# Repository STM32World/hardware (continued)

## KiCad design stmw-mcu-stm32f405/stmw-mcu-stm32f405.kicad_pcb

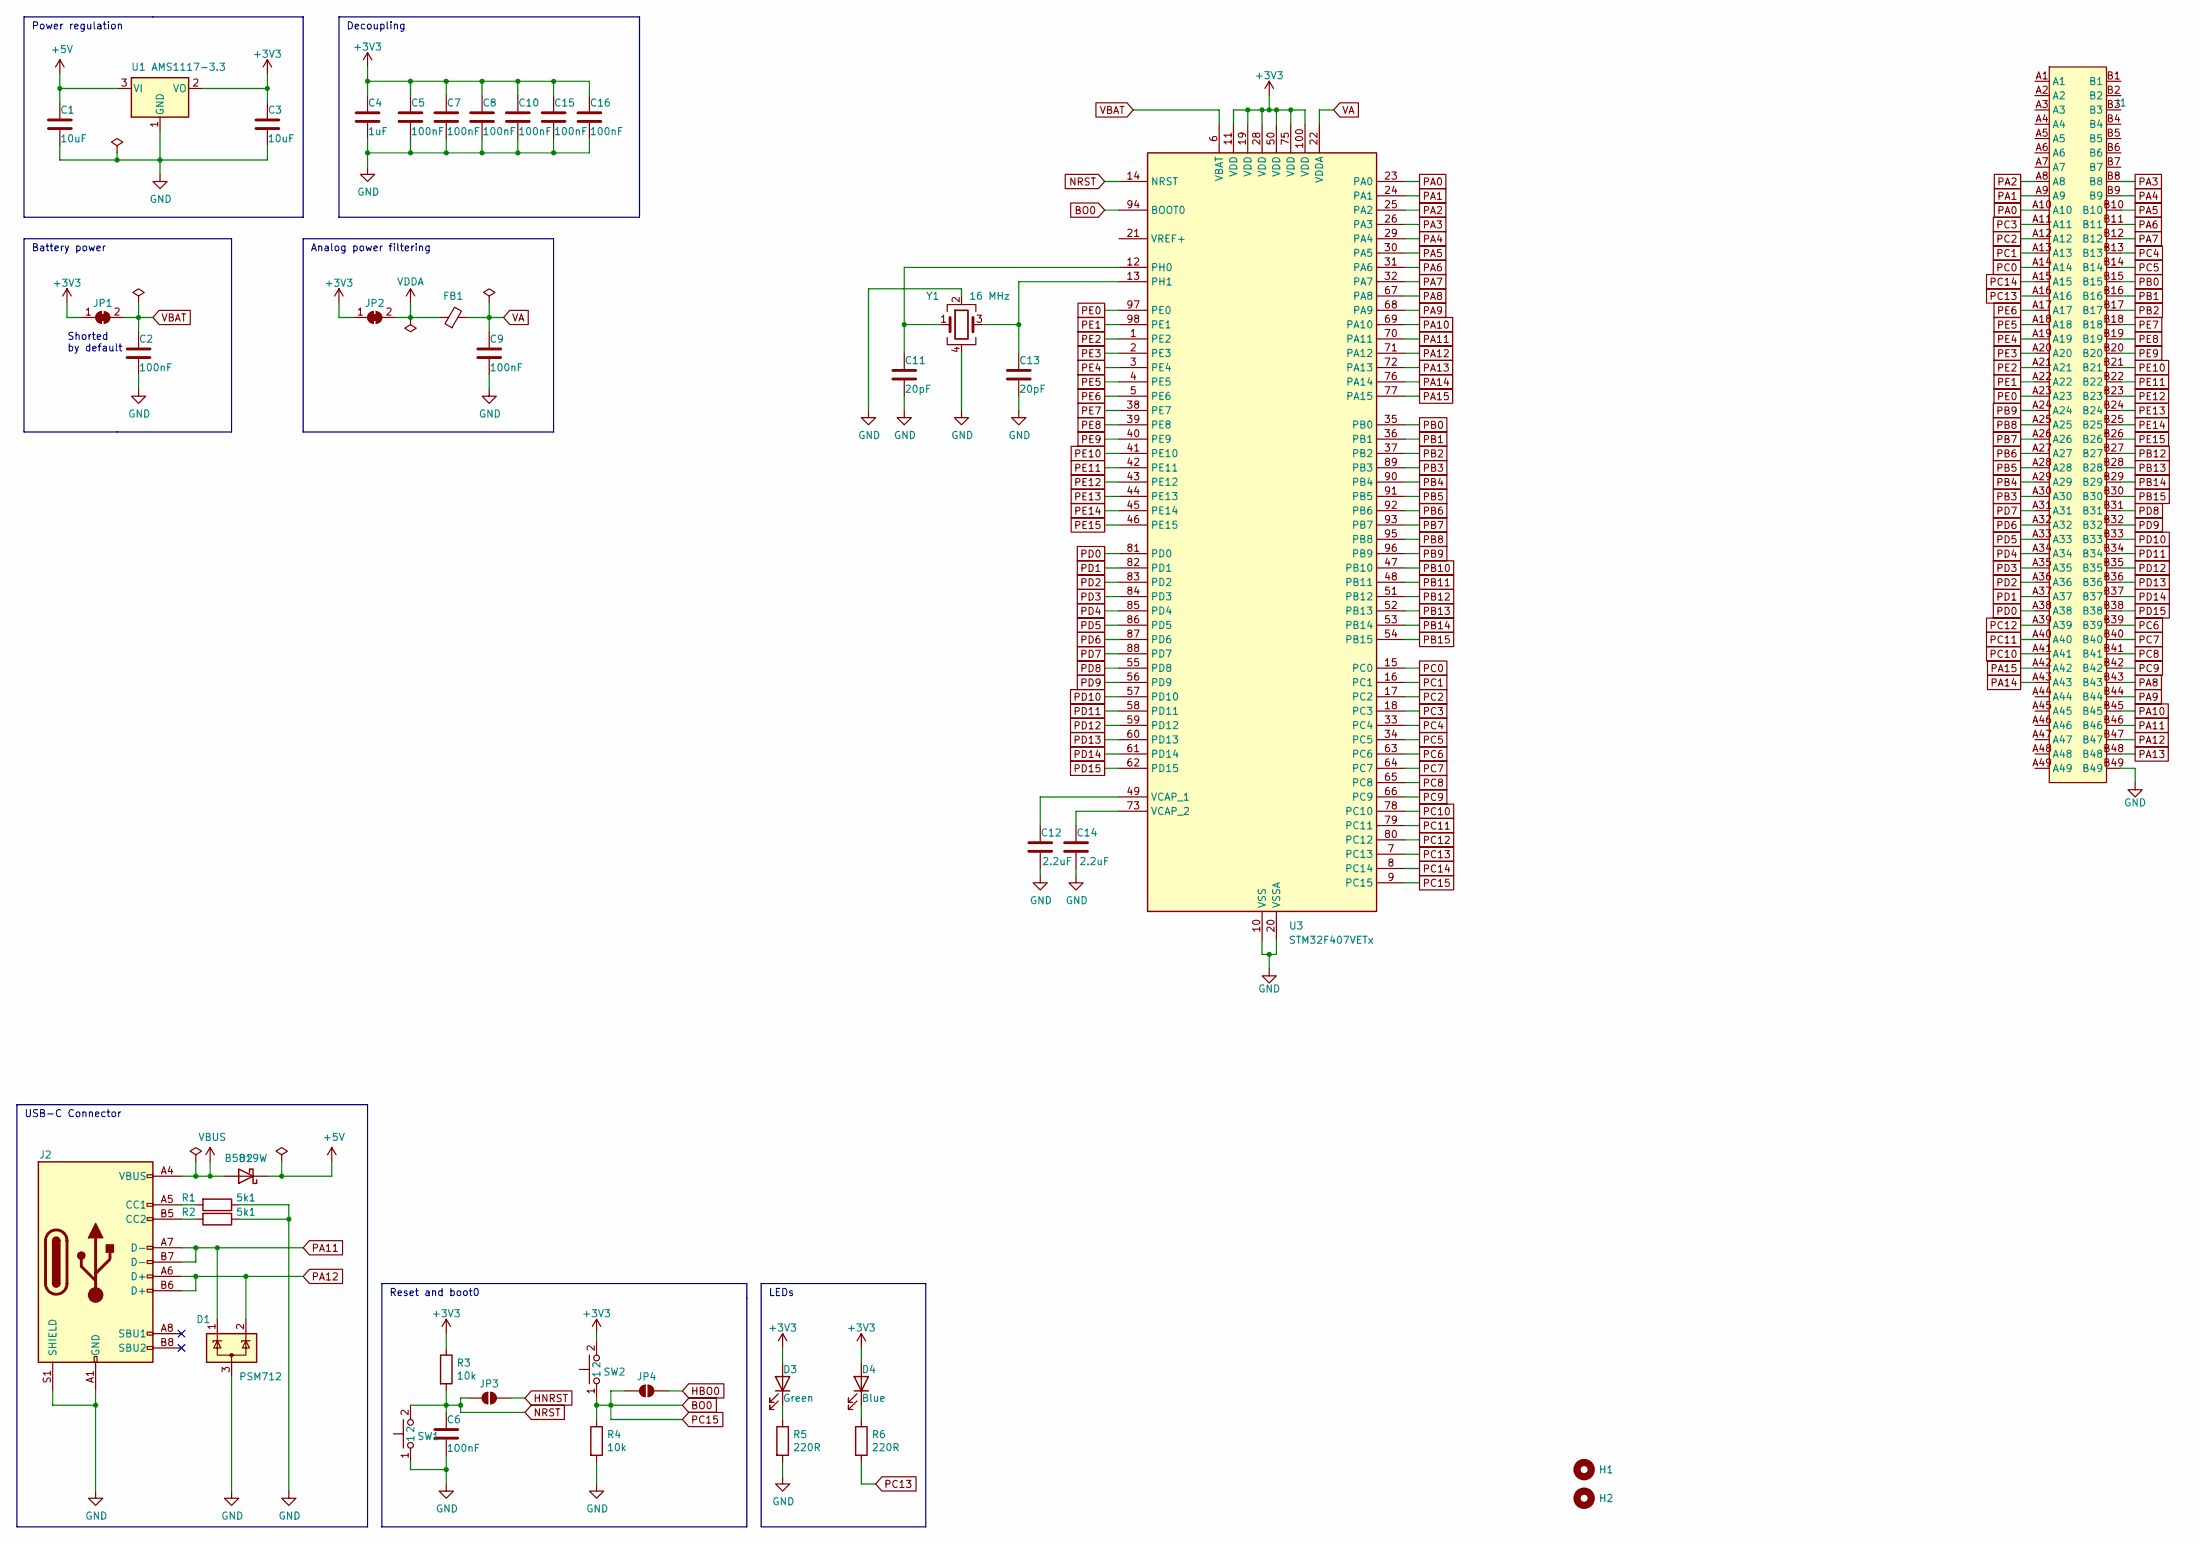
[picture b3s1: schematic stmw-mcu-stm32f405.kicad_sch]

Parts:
C1, C3: C_10UF_0805; C_0805_2012Metric; LCSC C15850
C2, C5, C6, C7, C8, C9, C10, C15, C16: C_100NF_0603; C_0603_1608Metric; LCSC C14663
C4: C_1UF_0603; C_0603_1608Metric; LCSC C15849
C11, C13: C_20PF_0603; C_0603_1608Metric; LCSC C1648
C12, C14: 2.2uF; C_0603_1608Metric; LCSC C23630
D1: PSM712; SOT-23; LCSC C32677
D2: B5819W; D_SOD-123; LCSC C8598
D3: LED_GREEN_0603; LED_0603_1608Metric; LCSC C19171301
D4: LED_BLUE_0603; LED_0603_1608Metric; LCSC C2288
FB1: FB_0603; L_0603_1608Metric; LCSC C1002
H1, H2: MountingHole; MountingHole_2.2mm_M2
J1: STMW_Board
J2: TYPE-C-31-M-12; USB_C_Receptacle_HRO_TYPE-C-31-M-12; LCSC C165948
JP1, JP2: SolderJumper_2_Bridged; SolderJumper-2_P1.3mm_Bridged_RoundedPad1.0x1.5mm
JP3, JP4: SolderJumper_2_Open; SolderJumper-2_P1.3mm_Open_RoundedPad1.0x1.5mm
R1, R2: R_5.1K_0603; R_0603_1608Metric; LCSC C23186
R3, R4: R_10K_0603; R_0603_1608Metric; LCSC C25804
R5, R6: R_220_0603; R_0603_1608Metric; LCSC C22962
SW1, SW2: TS-1088R-02526; LCSC C455281
U1: AMS1117-3.3; SOT-223-3_TabPin2; LCSC C6186
U3: STM32F407VETx; LQFP-100_14x14mm_P0.5mm; LCSC C28730
Y1: X_16MHZ; Crystal_SMD_3225-4Pin_3.2x2.5mm; LCSC C13738

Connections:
+3V3: C3.1, C4.1, C5.1, C7.1, C8.1, C10.1, C15.1, C16.1, D3.2 (A), D4.2 (A), JP1.1 (A), JP2.1 (A), R3.1, SW2.2, U1.2 (VO), U3.11 (VDD), U3.19 (VDD), U3.28 (VDD), U3.50 (VDD), U3.75 (VDD), U3.100 (VDD)
+5V: C1.1, D2.1 (K), U1.3 (VI)
BO0: JP4.1 (A), R4.1, SW2.1, U3.9 (PC15), U3.94 (BOOT0)
GND: C1.2, C2.2, C3.2, C4.2, C5.2, C6.2, C7.2, C8.2, C9.2, C10.2, C11.2, C12.2, C13.2, C14.2, C15.2, C16.2, D1.3 (A), J1.B49, J2.A1 (GND), J2.A12 (GND), J2.B1 (GND), J2.B12 (GND), J2.S1 (SHIELD), R1.1, R2.1, R4.2, R5.2, SW1.1, U1.1 (GND), U3.10 (VSS), U3.20 (VSSA), U3.27 (VSS), U3.74 (VSS), U3.99 (VSS), Y1.2, Y1.4
HBO0: JP4.2 (B)
HNRST: JP3.2 (B)
NRST: C6.1, JP3.1 (A), R3.2, SW1.2, U3.14 (NRST)
unnamed: D3.1 (K), R5.1
unnamed: D4.1 (K), R6.1
unnamed: J2.A5 (CC1), R1.2
unnamed: J2.B5 (CC2), R2.2
unnamed: C11.1, U3.12 (PH0), Y1.1
unnamed: C13.1, U3.13 (PH1), Y1.3
unnamed: C12.1, U3.49 (VCAP_1)
unnamed: C14.1, U3.73 (VCAP_2)
PA0: J1.A10, U3.23 (PA0)
PA1: J1.A9, U3.24 (PA1)
PA2: J1.A8, U3.25 (PA2)
PA3: J1.B8, U3.26 (PA3)
PA4: J1.B9, U3.29 (PA4)
PA5: J1.B10, U3.30 (PA5)
PA6: J1.B11, U3.31 (PA6)
PA7: J1.B12, U3.32 (PA7)
PA8: J1.B43, U3.67 (PA8)
PA9: J1.B44, U3.68 (PA9)
PA10: J1.B45, U3.69 (PA10)
PA11: D1.1 (K), J1.B46, J2.A7 (D-), J2.B7 (D-), U3.70 (PA11)
PA12: D1.2 (K), J1.B47, J2.A6 (D+), J2.B6 (D+), U3.71 (PA12)
PA13: J1.B48, U3.72 (PA13)
PA14: J1.A43, U3.76 (PA14)
PA15: J1.A42, U3.77 (PA15)
PB0: J1.B15, U3.35 (PB0)
PB1: J1.B16, U3.36 (PB1)
PB2: J1.B17, U3.37 (PB2)
PB3: J1.A30, U3.89 (PB3)
PB4: J1.A29, U3.90 (PB4)
PB5: J1.A28, U3.91 (PB5)
PB6: J1.A27, U3.92 (PB6)
PB7: J1.A26, U3.93 (PB7)
PB8: J1.A25, U3.95 (PB8)
PB9: J1.A24, U3.96 (PB9)
PB10: U3.47 (PB10)
PB11: U3.48 (PB11)
PB12: J1.B27, U3.51 (PB12)
PB13: J1.B28, U3.52 (PB13)
PB14: J1.B29, U3.53 (PB14)
PB15: J1.B30, U3.54 (PB15)
PC0: J1.A14, U3.15 (PC0)
PC1: J1.A13, U3.16 (PC1)
PC2: J1.A12, U3.17 (PC2)
PC3: J1.A11, U3.18 (PC3)
PC4: J1.B13, U3.33 (PC4)
PC5: J1.B14, U3.34 (PC5)
PC6: J1.B39, U3.63 (PC6)
PC7: J1.B40, U3.64 (PC7)
PC8: J1.B41, U3.65 (PC8)
PC9: J1.B42, U3.66 (PC9)
PC10: J1.A41, U3.78 (PC10)
PC11: J1.A40, U3.79 (PC11)
PC12: J1.A39, U3.80 (PC12)
PC13: J1.A16, R6.2, U3.7 (PC13)
PC14: J1.A15, U3.8 (PC14)
PD0: J1.A38, U3.81 (PD0)
PD1: J1.A37, U3.82 (PD1)
PD2: J1.A36, U3.83 (PD2)
PD3: J1.A35, U3.84 (PD3)
PD4: J1.A34, U3.85 (PD4)
PD5: J1.A33, U3.86 (PD5)
PD6: J1.A32, U3.87 (PD6)
PD7: J1.A31, U3.88 (PD7)
PD8: J1.B31, U3.55 (PD8)
PD9: J1.B32, U3.56 (PD9)
PD10: J1.B33, U3.57 (PD10)
PD11: J1.B34, U3.58 (PD11)
PD12: J1.B35, U3.59 (PD12)
PD13: J1.B36, U3.60 (PD13)
PD14: J1.B37, U3.61 (PD14)
PD15: J1.B38, U3.62 (PD15)
PE0: J1.A23, U3.97 (PE0)
PE1: J1.A22, U3.98 (PE1)
PE2: J1.A21, U3.1 (PE2)
PE3: J1.A20, U3.2 (PE3)
PE4: J1.A19, U3.3 (PE4)
PE5: J1.A18, U3.4 (PE5)
PE6: J1.A17, U3.5 (PE6)
PE7: J1.B18, U3.38 (PE7)
PE8: J1.B19, U3.39 (PE8)
PE9: J1.B20, U3.40 (PE9)
PE10: J1.B21, U3.41 (PE10)
PE11: J1.B22, U3.42 (PE11)
PE12: J1.B23, U3.43 (PE12)
PE13: J1.B24, U3.44 (PE13)
PE14: J1.B25, U3.45 (PE14)
PE15: J1.B26, U3.46 (PE15)
VA: C9.1, FB1.2, U3.22 (VDDA)
VBAT: C2.1, JP1.2 (B), U3.6 (VBAT)
VBUS: D2.2 (A), J2.A4 (VBUS), J2.A9 (VBUS), J2.B4 (VBUS), J2.B9 (VBUS)
VDDA: FB1.1, JP2.2 (B)

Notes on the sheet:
Analog power filtering
Decoupling
Power regulation
USB-C Connector
LEDs
Reset and boot0
Battery power
Shorted by default

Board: 4 copper layers, 40 parts (2 on the bottom side), 94 nets, no tracks yet.

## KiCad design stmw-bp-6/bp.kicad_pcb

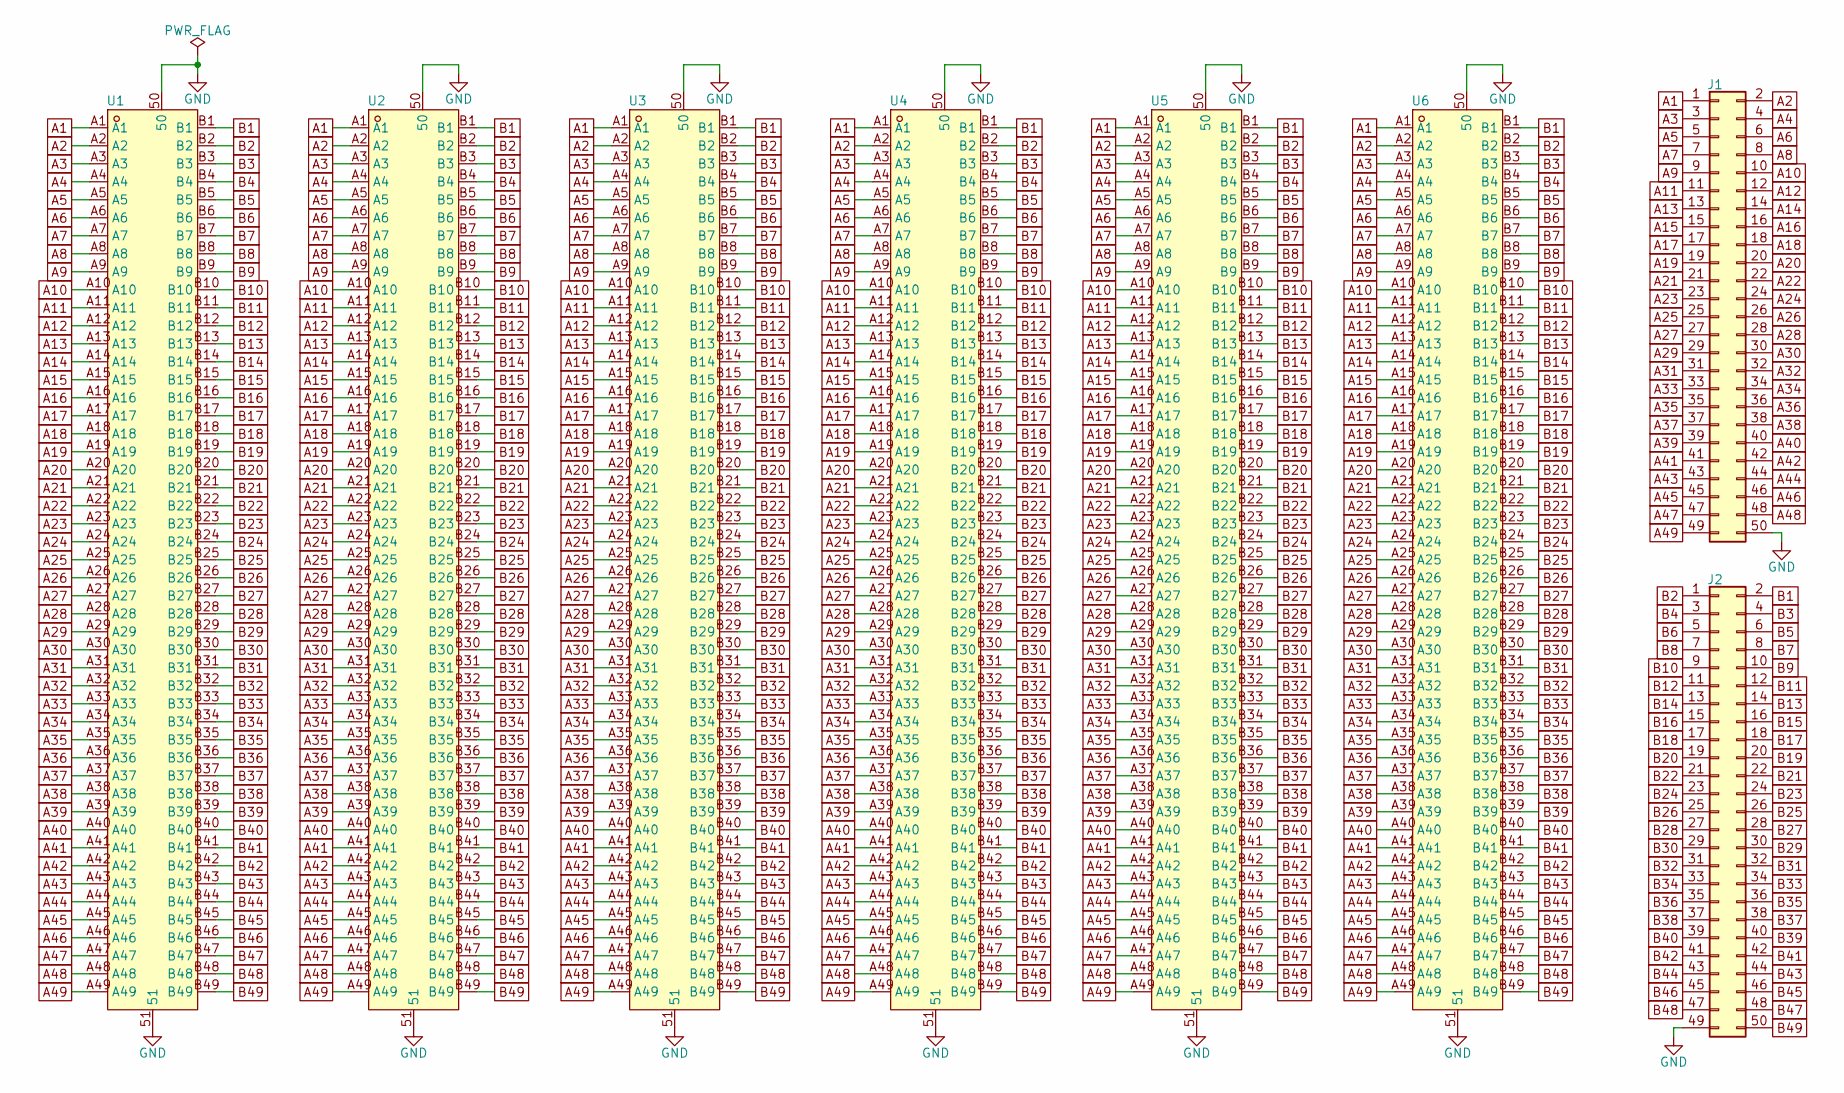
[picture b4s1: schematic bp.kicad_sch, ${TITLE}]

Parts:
J1: Conn_02x25_Odd_Even; IDC-Header_2x25_P2.54mm_Vertical
J2: Conn_02x25_Odd_Even; PinHeader_2x25_P2.54mm_Vertical
U1, U2, U3, U4, U5, U6: X1611WVS-98-9TV01; CONN-SMD_98P-P1.00-V_3133; LCSC C21263085

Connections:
A1: J1.1, U1.A1, U2.A1, U3.A1, U4.A1, U5.A1, U6.A1
A2: J1.2, U1.A2, U2.A2, U3.A2, U4.A2, U5.A2, U6.A2
A3: J1.3, U1.A3, U2.A3, U3.A3, U4.A3, U5.A3, U6.A3
A4: J1.4, U1.A4, U2.A4, U3.A4, U4.A4, U5.A4, U6.A4
A5: J1.5, U1.A5, U2.A5, U3.A5, U4.A5, U5.A5, U6.A5
A6: J1.6, U1.A6, U2.A6, U3.A6, U4.A6, U5.A6, U6.A6
A7: J1.7, U1.A7, U2.A7, U3.A7, U4.A7, U5.A7, U6.A7
A8: J1.8, U1.A8, U2.A8, U3.A8, U4.A8, U5.A8, U6.A8
A9: J1.9, U1.A9, U2.A9, U3.A9, U4.A9, U5.A9, U6.A9
A10: J1.10, U1.A10, U2.A10, U3.A10, U4.A10, U5.A10, U6.A10
A11: J1.11, U1.A11, U2.A11, U3.A11, U4.A11, U5.A11, U6.A11
A12: J1.12, U1.A12, U2.A12, U3.A12, U4.A12, U5.A12, U6.A12
A13: J1.13, U1.A13, U2.A13, U3.A13, U4.A13, U5.A13, U6.A13
A14: J1.14, U1.A14, U2.A14, U3.A14, U4.A14, U5.A14, U6.A14
A15: J1.15, U1.A15, U2.A15, U3.A15, U4.A15, U5.A15, U6.A15
A16: J1.16, U1.A16, U2.A16, U3.A16, U4.A16, U5.A16, U6.A16
A17: J1.17, U1.A17, U2.A17, U3.A17, U4.A17, U5.A17, U6.A17
A18: J1.18, U1.A18, U2.A18, U3.A18, U4.A18, U5.A18, U6.A18
A19: J1.19, U1.A19, U2.A19, U3.A19, U4.A19, U5.A19, U6.A19
A20: J1.20, U1.A20, U2.A20, U3.A20, U4.A20, U5.A20, U6.A20
A21: J1.21, U1.A21, U2.A21, U3.A21, U4.A21, U5.A21, U6.A21
A22: J1.22, U1.A22, U2.A22, U3.A22, U4.A22, U5.A22, U6.A22
A23: J1.23, U1.A23, U2.A23, U3.A23, U4.A23, U5.A23, U6.A23
A24: J1.24, U1.A24, U2.A24, U3.A24, U4.A24, U5.A24, U6.A24
A25: J1.25, U1.A25, U2.A25, U3.A25, U4.A25, U5.A25, U6.A25
A26: J1.26, U1.A26, U2.A26, U3.A26, U4.A26, U5.A26, U6.A26
A27: J1.27, U1.A27, U2.A27, U3.A27, U4.A27, U5.A27, U6.A27
A28: J1.28, U1.A28, U2.A28, U3.A28, U4.A28, U5.A28, U6.A28
A29: J1.29, U1.A29, U2.A29, U3.A29, U4.A29, U5.A29, U6.A29
A30: J1.30, U1.A30, U2.A30, U3.A30, U4.A30, U5.A30, U6.A30
A31: J1.31, U1.A31, U2.A31, U3.A31, U4.A31, U5.A31, U6.A31
A32: J1.32, U1.A32, U2.A32, U3.A32, U4.A32, U5.A32, U6.A32
A33: J1.33, U1.A33, U2.A33, U3.A33, U4.A33, U5.A33, U6.A33
A34: J1.34, U1.A34, U2.A34, U3.A34, U4.A34, U5.A34, U6.A34
A35: J1.35, U1.A35, U2.A35, U3.A35, U4.A35, U5.A35, U6.A35
A36: J1.36, U1.A36, U2.A36, U3.A36, U4.A36, U5.A36, U6.A36
A37: J1.37, U1.A37, U2.A37, U3.A37, U4.A37, U5.A37, U6.A37
A38: J1.38, U1.A38, U2.A38, U3.A38, U4.A38, U5.A38, U6.A38
A39: J1.39, U1.A39, U2.A39, U3.A39, U4.A39, U5.A39, U6.A39
A40: J1.40, U1.A40, U2.A40, U3.A40, U4.A40, U5.A40, U6.A40
A41: J1.41, U1.A41, U2.A41, U3.A41, U4.A41, U5.A41, U6.A41
A42: J1.42, U1.A42, U2.A42, U3.A42, U4.A42, U5.A42, U6.A42
A43: J1.43, U1.A43, U2.A43, U3.A43, U4.A43, U5.A43, U6.A43
A44: J1.44, U1.A44, U2.A44, U3.A44, U4.A44, U5.A44, U6.A44
A45: J1.45, U1.A45, U2.A45, U3.A45, U4.A45, U5.A45, U6.A45
A46: J1.46, U1.A46, U2.A46, U3.A46, U4.A46, U5.A46, U6.A46
A47: J1.47, U1.A47, U2.A47, U3.A47, U4.A47, U5.A47, U6.A47
A48: J1.48, U1.A48, U2.A48, U3.A48, U4.A48, U5.A48, U6.A48
A49: J1.49, U1.A49, U2.A49, U3.A49, U4.A49, U5.A49, U6.A49
B1: J2.2, U1.B1, U2.B1, U3.B1, U4.B1, U5.B1, U6.B1
B2: J2.1, U1.B2, U2.B2, U3.B2, U4.B2, U5.B2, U6.B2
B3: J2.4, U1.B3, U2.B3, U3.B3, U4.B3, U5.B3, U6.B3
B4: J2.3, U1.B4, U2.B4, U3.B4, U4.B4, U5.B4, U6.B4
B5: J2.6, U1.B5, U2.B5, U3.B5, U4.B5, U5.B5, U6.B5
B6: J2.5, U1.B6, U2.B6, U3.B6, U4.B6, U5.B6, U6.B6
B7: J2.8, U1.B7, U2.B7, U3.B7, U4.B7, U5.B7, U6.B7
B8: J2.7, U1.B8, U2.B8, U3.B8, U4.B8, U5.B8, U6.B8
B9: J2.10, U1.B9, U2.B9, U3.B9, U4.B9, U5.B9, U6.B9
B10: J2.9, U1.B10, U2.B10, U3.B10, U4.B10, U5.B10, U6.B10
B11: J2.12, U1.B11, U2.B11, U3.B11, U4.B11, U5.B11, U6.B11
B12: J2.11, U1.B12, U2.B12, U3.B12, U4.B12, U5.B12, U6.B12
B13: J2.14, U1.B13, U2.B13, U3.B13, U4.B13, U5.B13, U6.B13
B14: J2.13, U1.B14, U2.B14, U3.B14, U4.B14, U5.B14, U6.B14
B15: J2.16, U1.B15, U2.B15, U3.B15, U4.B15, U5.B15, U6.B15
B16: J2.15, U1.B16, U2.B16, U3.B16, U4.B16, U5.B16, U6.B16
B17: J2.18, U1.B17, U2.B17, U3.B17, U4.B17, U5.B17, U6.B17
B18: J2.17, U1.B18, U2.B18, U3.B18, U4.B18, U5.B18, U6.B18
B19: J2.20, U1.B19, U2.B19, U3.B19, U4.B19, U5.B19, U6.B19
B20: J2.19, U1.B20, U2.B20, U3.B20, U4.B20, U5.B20, U6.B20
B21: J2.22, U1.B21, U2.B21, U3.B21, U4.B21, U5.B21, U6.B21
B22: J2.21, U1.B22, U2.B22, U3.B22, U4.B22, U5.B22, U6.B22
B23: J2.24, U1.B23, U2.B23, U3.B23, U4.B23, U5.B23, U6.B23
B24: J2.23, U1.B24, U2.B24, U3.B24, U4.B24, U5.B24, U6.B24
B25: J2.26, U1.B25, U2.B25, U3.B25, U4.B25, U5.B25, U6.B25
B26: J2.25, U1.B26, U2.B26, U3.B26, U4.B26, U5.B26, U6.B26
B27: J2.28, U1.B27, U2.B27, U3.B27, U4.B27, U5.B27, U6.B27
B28: J2.27, U1.B28, U2.B28, U3.B28, U4.B28, U5.B28, U6.B28
B29: J2.30, U1.B29, U2.B29, U3.B29, U4.B29, U5.B29, U6.B29
B30: J2.29, U1.B30, U2.B30, U3.B30, U4.B30, U5.B30, U6.B30
B31: J2.32, U1.B31, U2.B31, U3.B31, U4.B31, U5.B31, U6.B31
B32: J2.31, U1.B32, U2.B32, U3.B32, U4.B32, U5.B32, U6.B32
B33: J2.34, U1.B33, U2.B33, U3.B33, U4.B33, U5.B33, U6.B33
B34: J2.33, U1.B34, U2.B34, U3.B34, U4.B34, U5.B34, U6.B34
B35: J2.36, U1.B35, U2.B35, U3.B35, U4.B35, U5.B35, U6.B35
B36: J2.35, U1.B36, U2.B36, U3.B36, U4.B36, U5.B36, U6.B36
B37: J2.38, U1.B37, U2.B37, U3.B37, U4.B37, U5.B37, U6.B37
B38: J2.37, U1.B38, U2.B38, U3.B38, U4.B38, U5.B38, U6.B38
B39: J2.40, U1.B39, U2.B39, U3.B39, U4.B39, U5.B39, U6.B39
B40: J2.39, U1.B40, U2.B40, U3.B40, U4.B40, U5.B40, U6.B40
B41: J2.42, U1.B41, U2.B41, U3.B41, U4.B41, U5.B41, U6.B41
B42: J2.41, U1.B42, U2.B42, U3.B42, U4.B42, U5.B42, U6.B42
B43: J2.44, U1.B43, U2.B43, U3.B43, U4.B43, U5.B43, U6.B43
B44: J2.43, U1.B44, U2.B44, U3.B44, U4.B44, U5.B44, U6.B44
B45: J2.46, U1.B45, U2.B45, U3.B45, U4.B45, U5.B45, U6.B45
B46: J2.45, U1.B46, U2.B46, U3.B46, U4.B46, U5.B46, U6.B46
B47: J2.48, U1.B47, U2.B47, U3.B47, U4.B47, U5.B47, U6.B47
B48: J2.47, U1.B48, U2.B48, U3.B48, U4.B48, U5.B48, U6.B48
B49: J2.50, U1.B49, U2.B49, U3.B49, U4.B49, U5.B49, U6.B49
GND: J1.50, J2.49, U1.50, U1.51, U2.50, U2.51, U3.50, U3.51, U4.50, U4.51, U5.50, U5.51, U6.50, U6.51

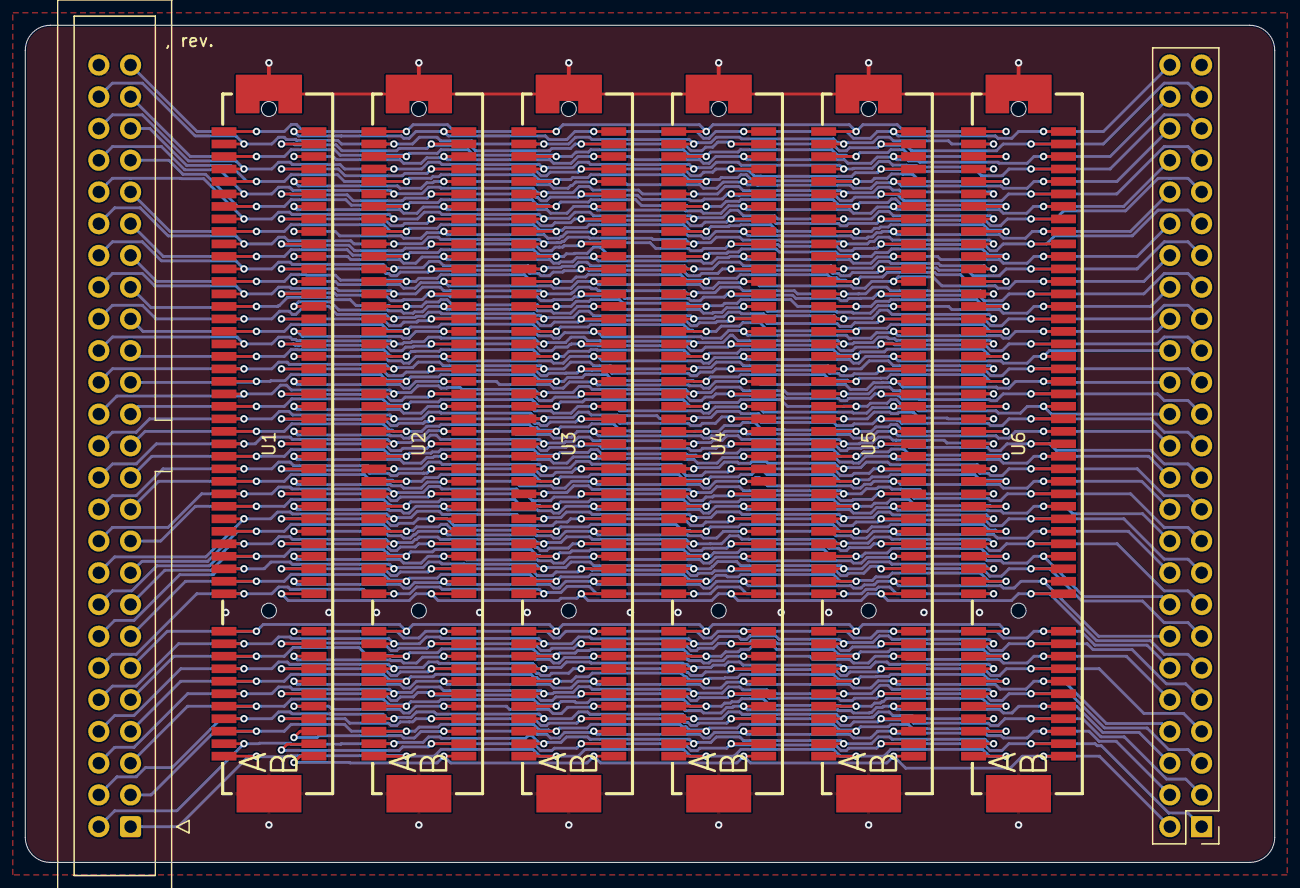
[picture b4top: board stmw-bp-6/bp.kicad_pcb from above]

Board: 2 copper layers, 100.0 x 67.0 mm, 8 parts (0 on the bottom side), 99 nets.

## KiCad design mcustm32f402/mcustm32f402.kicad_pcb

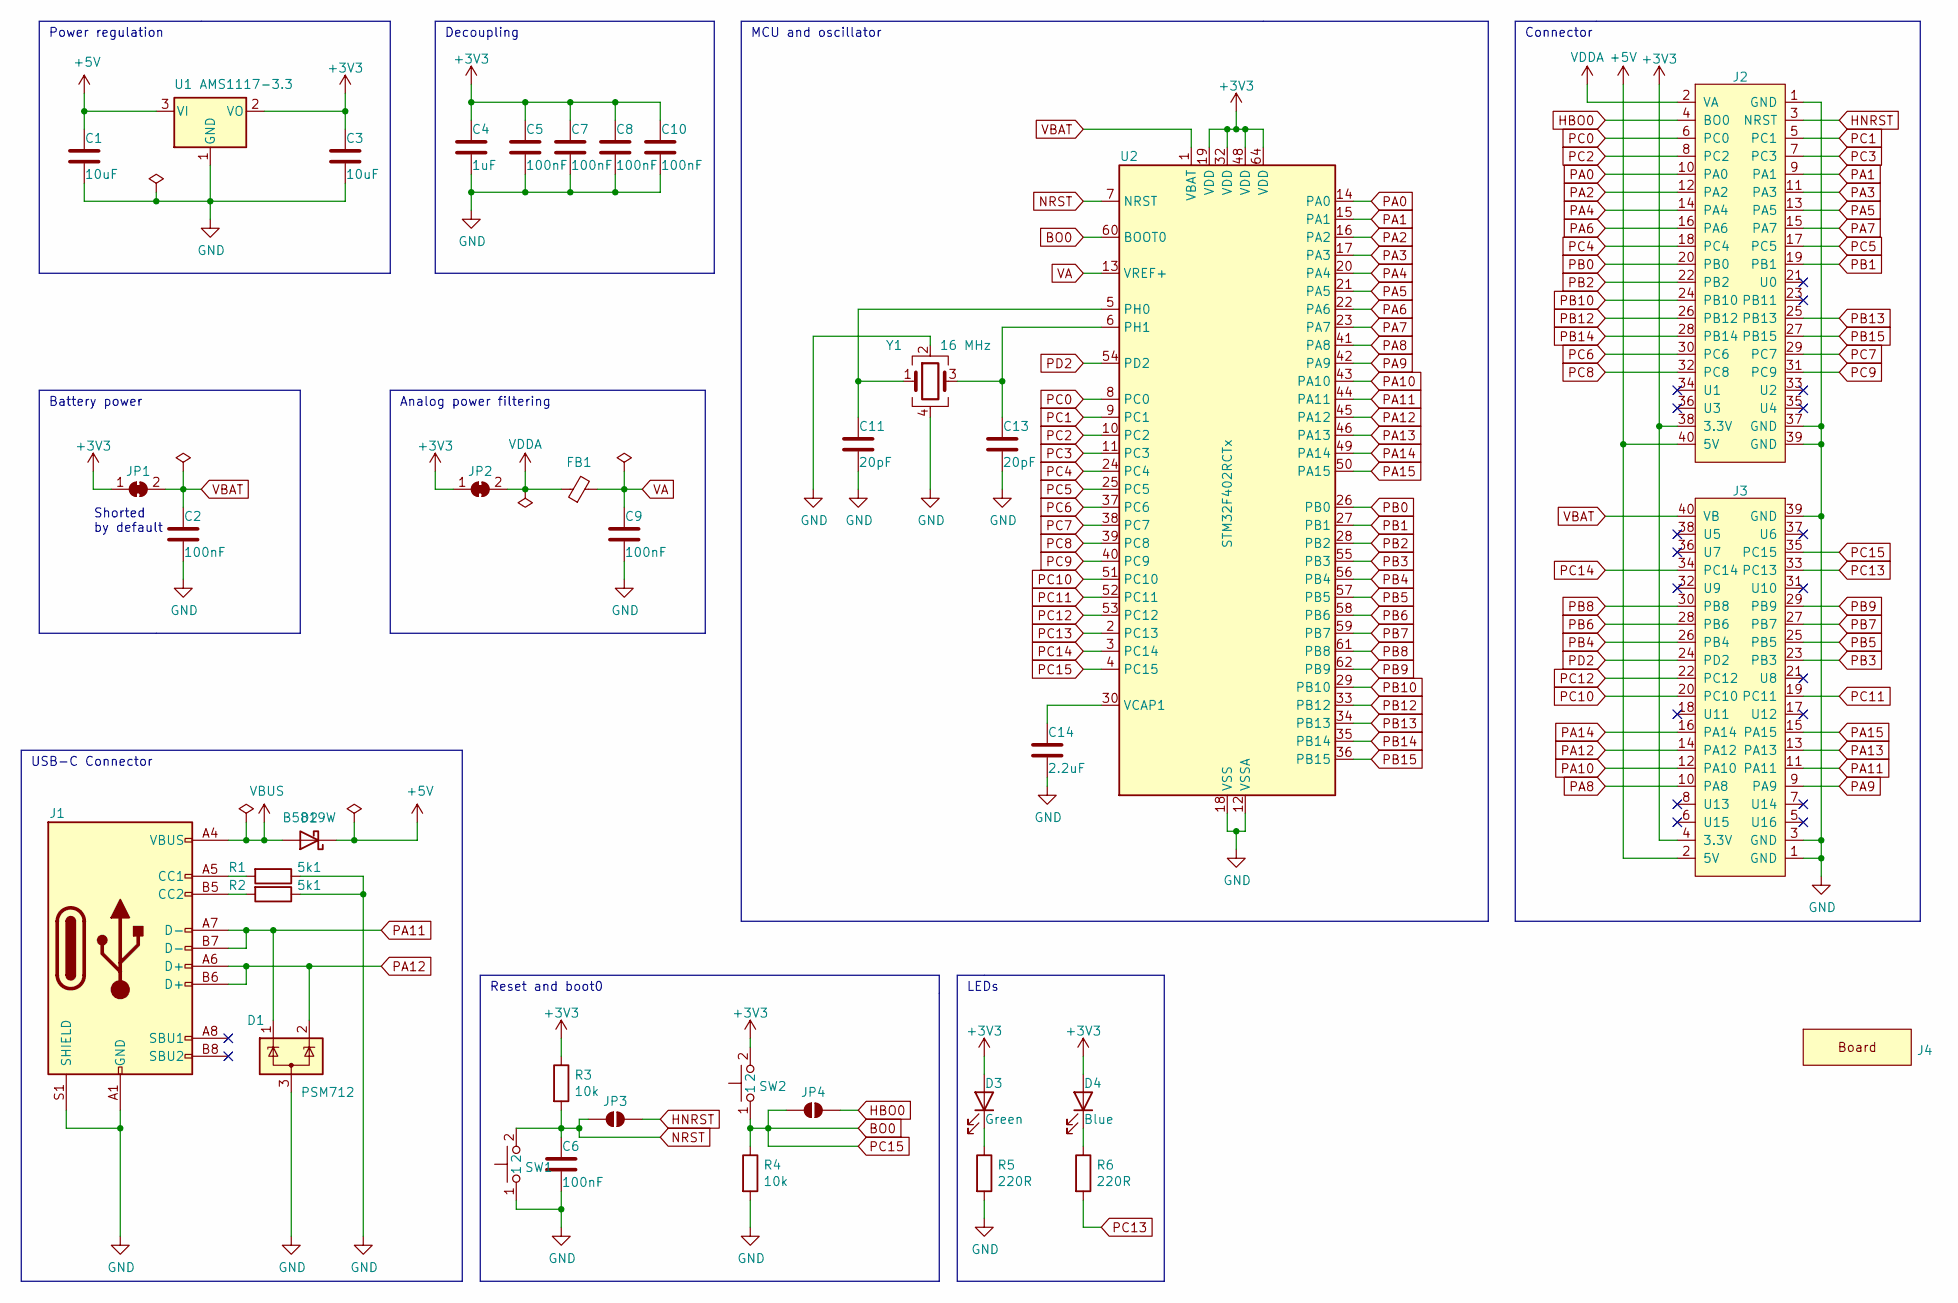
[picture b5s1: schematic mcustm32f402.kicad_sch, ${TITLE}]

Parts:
C1, C3: C_10UF_0805; C_0805_2012Metric; LCSC C15850
C2, C5, C6, C7, C8, C9, C10: C_100NF_0603; C_0603_1608Metric; LCSC C14663
C4: C_1UF_0603; C_0603_1608Metric; LCSC C15849
C11, C13: C_20PF_0603; C_0603_1608Metric; LCSC C1648
C14: C_2.2UF_0603; C_0603_1608Metric; LCSC C23630
D1: PSM712; SOT-23; LCSC C32677
D2: B5819W; D_SOD-123; LCSC C8598
D3: LED_GREEN_0603; LED_0603_1608Metric; LCSC C19171301
D4: LED_BLUE_0603; LED_0603_1608Metric; LCSC C2288
FB1: FB_0603; L_0603_1608Metric; LCSC C1002
J1: TYPE-C-31-M-12; USB_C_Receptacle_HRO_TYPE-C-31-M-12; LCSC C165948
J2: STM32WORLD_CONNECTOR_1; PinSocket_2x20_P2.54mm_Vertical_Stackable; LCSC C35165
J3: STM32WORLD_CONNECTOR_2; PinSocket_2x20_P2.54mm_Vertical_Stackable; LCSC C35165
J4: STM32WORLD_BOARD
JP1, JP2: SolderJumper_2_Bridged; SolderJumper-2_P1.3mm_Bridged_RoundedPad1.0x1.5mm
JP3, JP4: SolderJumper_2_Open; SolderJumper-2_P1.3mm_Open_RoundedPad1.0x1.5mm
R1, R2: R_5.1K_0603; R_0603_1608Metric; LCSC C23186
R3, R4: R_10K_0603; R_0603_1608Metric; LCSC C25804
R5, R6: R_220_0603; R_0603_1608Metric; LCSC C22962
SW1, SW2: TS-1088R-02526; LCSC C455281
U1: AMS1117-3.3; SOT-223-3_TabPin2; LCSC C6186
U2: STM32F402RCTx; LQFP-64_10x10mm_P0.5mm; LCSC C2915304
Y1: X_16MHZ; Crystal_SMD_3225-4Pin_3.2x2.5mm; LCSC C13738

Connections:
+3V3: C3.1, C4.1, C5.1, C7.1, C8.1, C10.1, D3.2 (A), D4.2 (A), J2.38 (3.3V), J3.4 (3.3V), JP1.1 (A), JP2.1 (A), R3.1, SW2.2, U1.2 (VO), U2.19 (VDD), U2.32 (VDD), U2.48 (VDD), U2.64 (VDD)
+5V: C1.1, D2.1 (K), J2.40 (5V), J3.2 (5V), U1.3 (VI)
BO0: J3.35 (PC15), JP4.1 (A), R4.1, SW2.1, U2.4 (PC15), U2.60 (BOOT0)
GND: C1.2, C2.2, C3.2, C4.2, C5.2, C6.2, C7.2, C8.2, C9.2, C10.2, C11.2, C13.2, C14.2, D1.3 (A), J1.A1 (GND), J1.A12 (GND), J1.B1 (GND), J1.B12 (GND), J1.S1 (SHIELD), J2.1 (GND), J2.37 (GND), J2.39 (GND), J3.1 (GND), J3.3 (GND), J3.39 (GND), R1.1, R2.1, R4.2, R5.2, SW1.1, U1.1 (GND), U2.12 (VSSA), U2.18 (VSS), U2.31 (VSS), U2.47 (VSS), U2.63 (VSS), Y1.2, Y1.4
HBO0: J2.4 (BO0), JP4.2 (B)
HNRST: J2.3 (NRST), JP3.2 (B)
NRST: C6.1, JP3.1 (A), R3.2, SW1.2, U2.7 (NRST)
unnamed: D3.1 (K), R5.1
unnamed: D4.1 (K), R6.1
unnamed: J1.A5 (CC1), R1.2
unnamed: J1.B5 (CC2), R2.2
unnamed: C11.1, U2.5 (PH0), Y1.1
unnamed: C13.1, U2.6 (PH1), Y1.3
unnamed: C14.1, U2.30 (VCAP1)
PA0: J2.10 (PA0), U2.14 (PA0)
PA1: J2.9 (PA1), U2.15 (PA1)
PA2: J2.12 (PA2), U2.16 (PA2)
PA3: J2.11 (PA3), U2.17 (PA3)
PA4: J2.14 (PA4), U2.20 (PA4)
PA5: J2.13 (PA5), U2.21 (PA5)
PA6: J2.16 (PA6), U2.22 (PA6)
PA7: J2.15 (PA7), U2.23 (PA7)
PA8: J3.10 (PA8), U2.41 (PA8)
PA9: J3.9 (PA9), U2.42 (PA9)
PA10: J3.12 (PA10), U2.43 (PA10)
PA11: D1.1 (K), J1.A7 (D-), J1.B7 (D-), J3.11 (PA11), U2.44 (PA11)
PA12: D1.2 (K), J1.A6 (D+), J1.B6 (D+), J3.14 (PA12), U2.45 (PA12)
PA13: J3.13 (PA13), U2.46 (PA13)
PA14: J3.16 (PA14), U2.49 (PA14)
PA15: J3.15 (PA15), U2.50 (PA15)
PB0: J2.20 (PB0), U2.26 (PB0)
PB1: J2.19 (PB1), U2.27 (PB1)
PB2: J2.22 (PB2), U2.28 (PB2)
PB3: J3.23 (PB3), U2.55 (PB3)
PB4: J3.26 (PB4), U2.56 (PB4)
PB5: J3.25 (PB5), U2.57 (PB5)
PB6: J3.28 (PB6), U2.58 (PB6)
PB7: J3.27 (PB7), U2.59 (PB7)
PB8: J3.30 (PB8), U2.61 (PB8)
PB9: J3.29 (PB9), U2.62 (PB9)
PB10: J2.24 (PB10), U2.29 (PB10)
PB12: J2.26 (PB12), U2.33 (PB12)
PB13: J2.25 (PB13), U2.34 (PB13)
PB14: J2.28 (PB14), U2.35 (PB14)
PB15: J2.27 (PB15), U2.36 (PB15)
PC0: J2.6 (PC0), U2.8 (PC0)
PC1: J2.5 (PC1), U2.9 (PC1)
PC2: J2.8 (PC2), U2.10 (PC2)
PC3: J2.7 (PC3), U2.11 (PC3)
PC4: J2.18 (PC4), U2.24 (PC4)
PC5: J2.17 (PC5), U2.25 (PC5)
PC6: J2.30 (PC6), U2.37 (PC6)
PC7: J2.29 (PC7), U2.38 (PC7)
PC8: J2.32 (PC8), U2.39 (PC8)
PC9: J2.31 (PC9), U2.40 (PC9)
PC10: J3.20 (PC10), U2.51 (PC10)
PC11: J3.19 (PC11), U2.52 (PC11)
PC12: J3.22 (PC12), U2.53 (PC12)
PC13: J3.33 (PC13), R6.2, U2.2 (PC13)
PC14: J3.34 (PC14), U2.3 (PC14)
PD2: J3.24 (PD2), U2.54 (PD2)
VA: C9.1, FB1.2, U2.13 (VREF+)
VBAT: C2.1, J3.40 (VB), JP1.2 (B), U2.1 (VBAT)
VBUS: D2.2 (A), J1.A4 (VBUS), J1.A9 (VBUS), J1.B4 (VBUS), J1.B9 (VBUS)
VDDA: FB1.1, J2.2 (VA), JP2.2 (B)

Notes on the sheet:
Connector
Power regulation
Analog power filtering
Shorted by default
Battery power
LEDs
Reset and boot0
USB-C Connector
MCU and oscillator
Decoupling

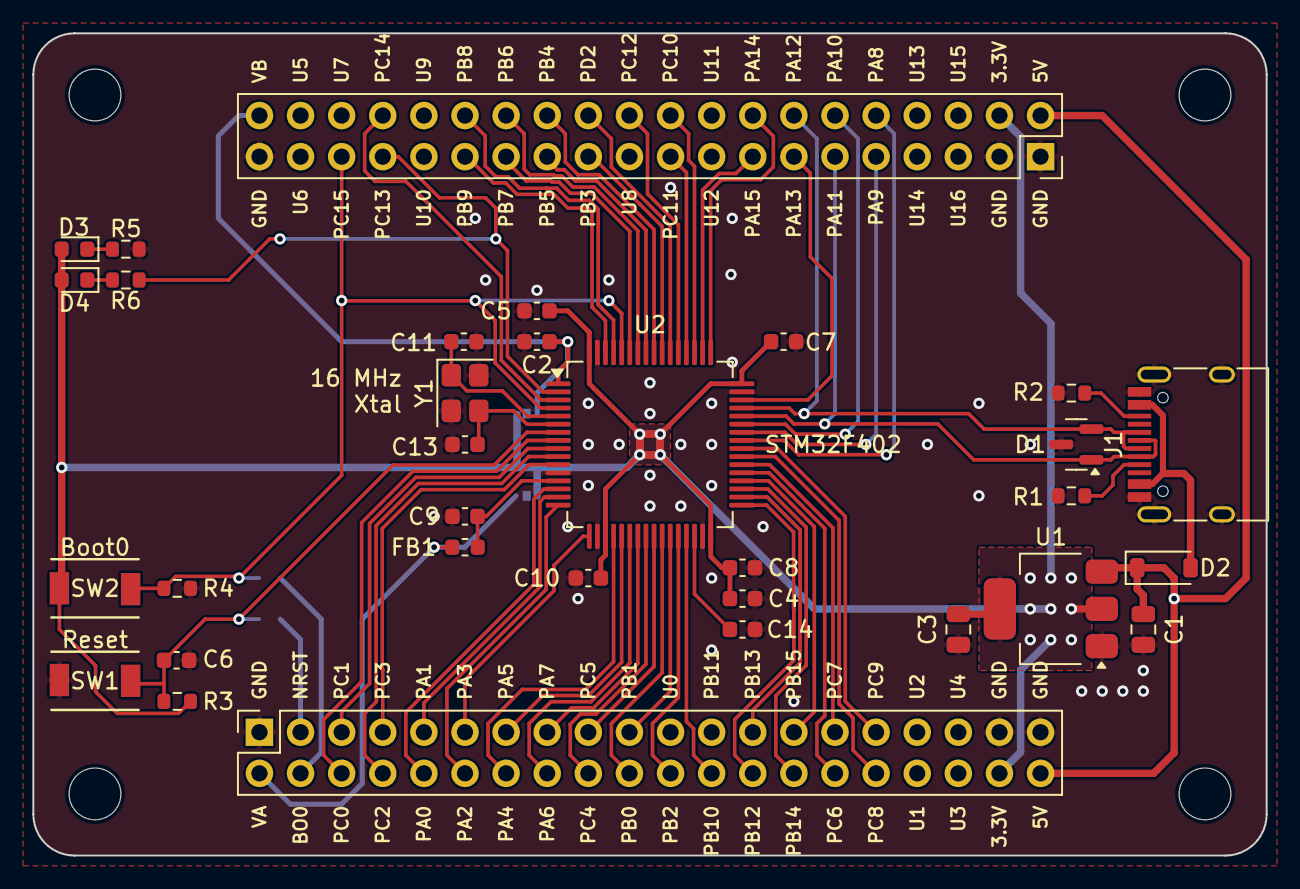
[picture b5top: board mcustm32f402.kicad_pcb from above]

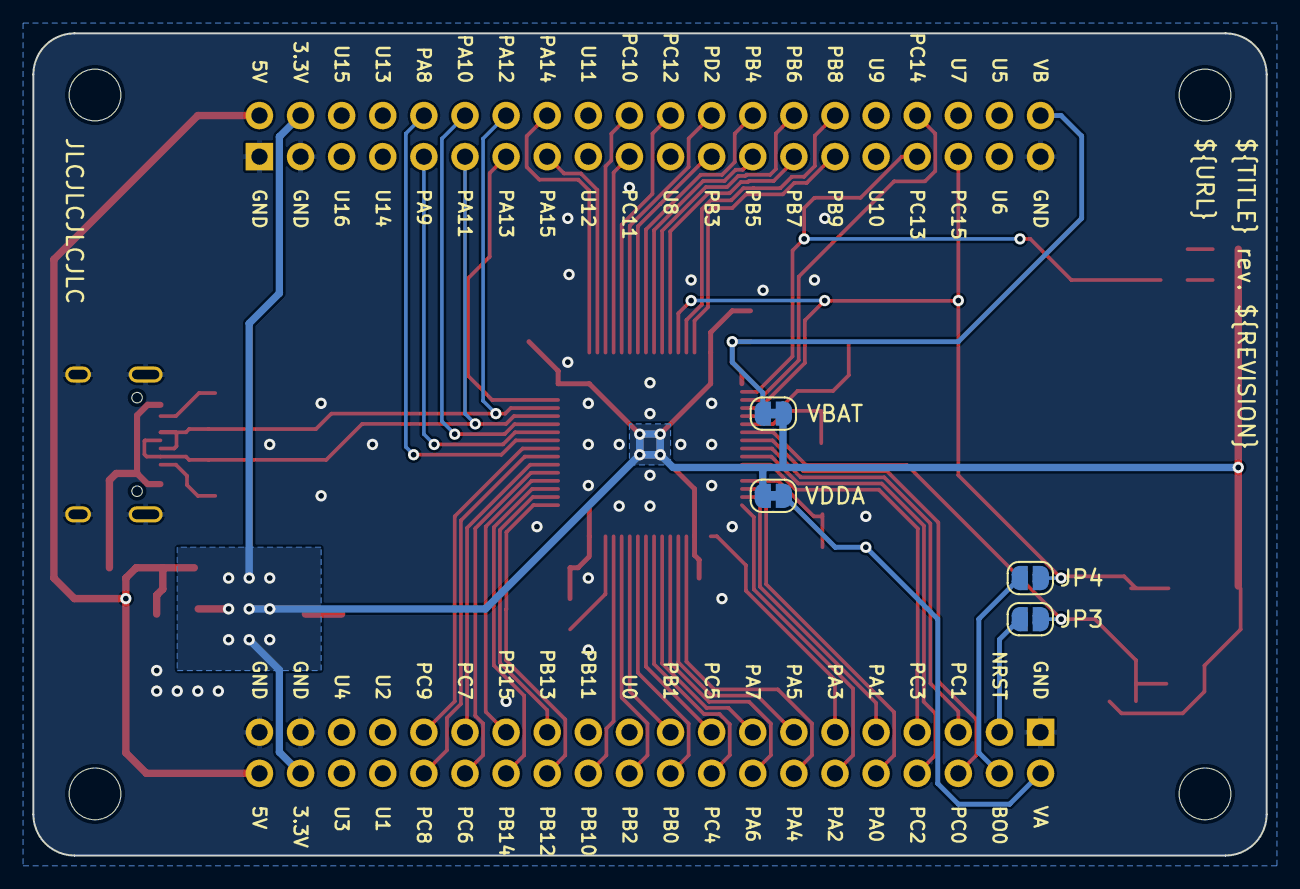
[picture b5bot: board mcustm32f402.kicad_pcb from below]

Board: 2 copper layers, 76.2 x 50.8 mm, 37 parts (4 on the bottom side), 65 nets.

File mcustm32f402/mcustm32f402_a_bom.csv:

"Reference","Value","Footprint","Qty","LCSC"
"C1,C3","C_10UF_0805","Capacitor_SMD:C_0805_2012Metric","2","C15850"
"C2,C5,C6,C7,C8,C9,C10","C_100NF_0603","Capacitor_SMD:C_0603_1608Metric","7","C14663"
"C4","C_1UF_0603","Capacitor_SMD:C_0603_1608Metric","1","C15849"
"C11,C13","C_20PF_0603","Capacitor_SMD:C_0603_1608Metric","2","C1648"
"C14","C_2.2UF_0603","Capacitor_SMD:C_0603_1608Metric","1","C23630"
"D1","PSM712","Package_TO_SOT_SMD:SOT-23","1","C32677"
"D2","B5819W","Diode_SMD:D_SOD-123","1","C8598"
"D3","LED_GREEN_0603","LED_SMD:LED_0603_1608Metric","1","C19171301"
"D4","LED_BLUE_0603","LED_SMD:LED_0603_1608Metric","1","C2288"
"FB1","FB_0603","Inductor_SMD:L_0603_1608Metric","1","C1002"
"J1","TYPE-C-31-M-12","stm32world:USB_C_Receptacle_HRO_TYPE-C-31-M-12","1","C165948"
"J2","STM32WORLD_CONNECTOR_1","stm32world:PinSocket_2x20_P2.54mm_Vertical_Stackable","1","C35165"
"J3","STM32WORLD_CONNECTOR_2","stm32world:PinSocket_2x20_P2.54mm_Vertical_Stackable","1","C35165"
"J4","STM32WORLD_BOARD","stm32world:STM32WORLD_BOARD","1",""
"JP1,JP2","SolderJumper_2_Bridged","Jumper:SolderJumper-2_P1.3mm_Bridged_RoundedPad1.0x1.5mm","2",""
"JP3,JP4","SolderJumper_2_Open","Jumper:SolderJumper-2_P1.3mm_Open_RoundedPad1.0x1.5mm","2",""
"R1,R2","R_5.1K_0603","Resistor_SMD:R_0603_1608Metric","2","C23186"
"R3,R4","R_10K_0603","Resistor_SMD:R_0603_1608Metric","2","C25804"
"R5,R6","R_220_0603","Resistor_SMD:R_0603_1608Metric","2","C22962"
"SW1,SW2","TS-1088R-02526","stm32world:TS-1088R-02526","2","C455281"
"U1","AMS1117-3.3","Package_TO_SOT_SMD:SOT-223-3_TabPin2","1","C6186"
"U2","STM32F402RCTx","Package_QFP:LQFP-64_10x10mm_P0.5mm","1","C2915304"
"Y1","X_16MHZ","Crystal:Crystal_SMD_3225-4Pin_3.2x2.5mm","1","C13738"
